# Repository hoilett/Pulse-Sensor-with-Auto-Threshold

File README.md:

# Pulse-Sensor-with-Auto-Threshold

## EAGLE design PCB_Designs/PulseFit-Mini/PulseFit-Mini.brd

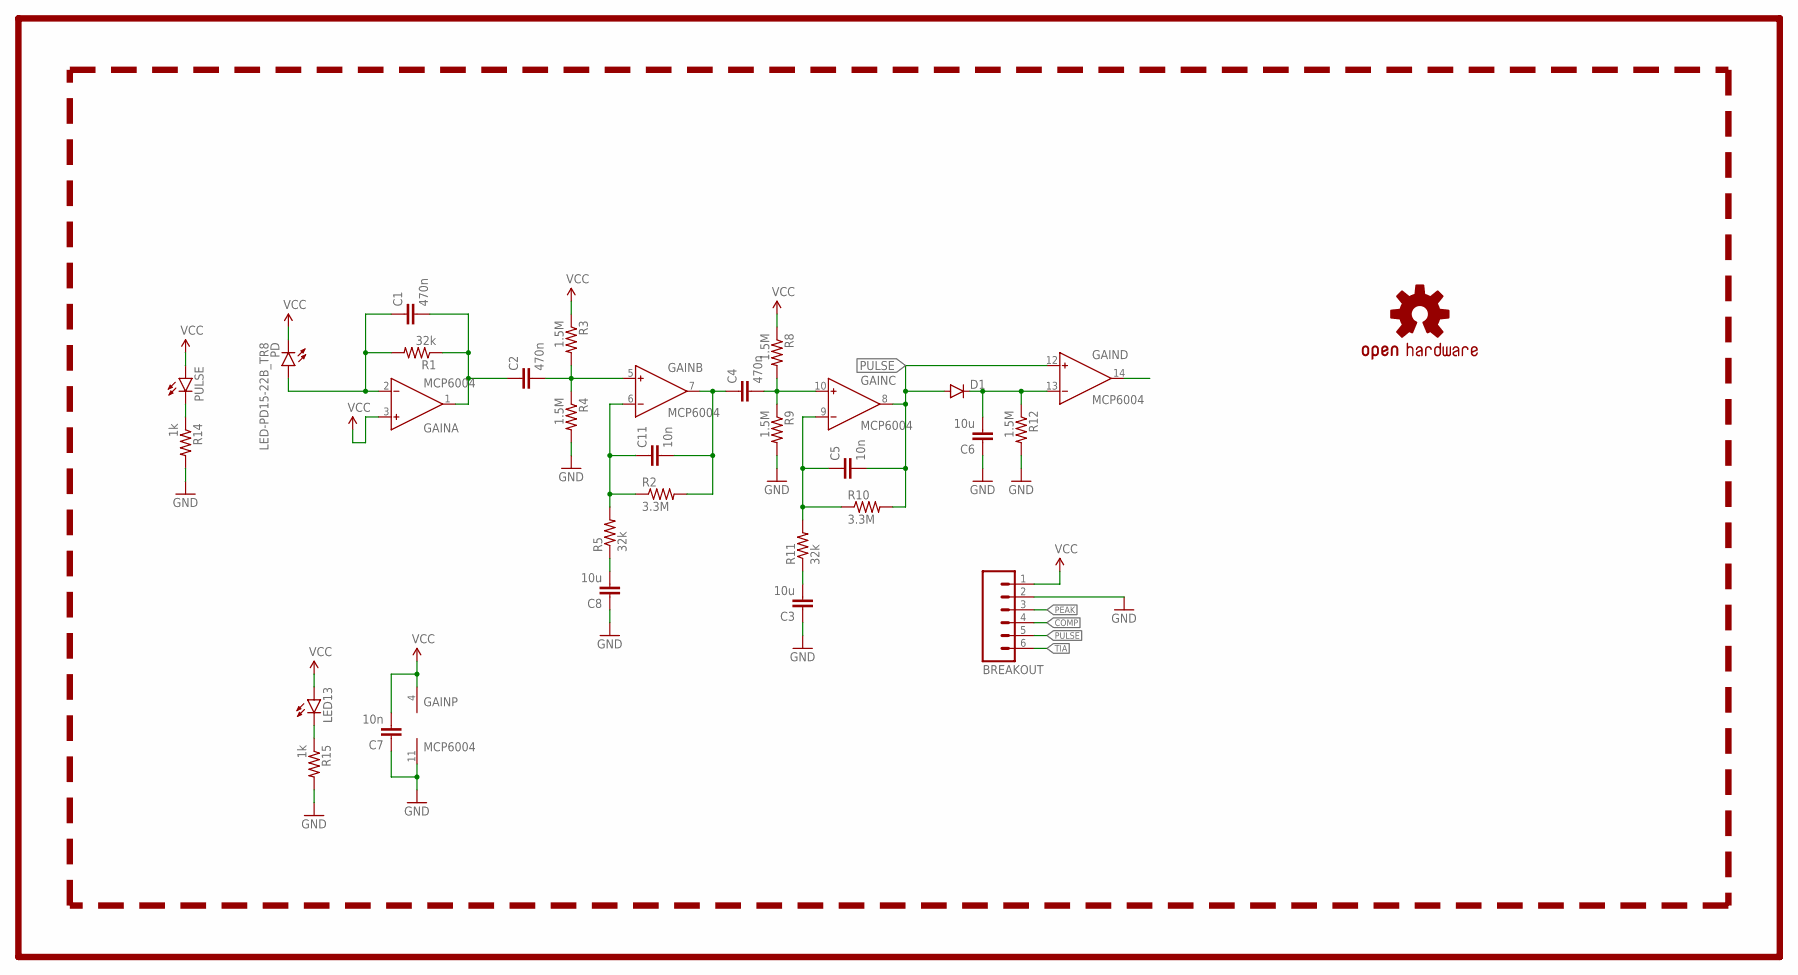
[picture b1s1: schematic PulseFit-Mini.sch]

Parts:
BREAKOUT: M06NO_SILK_FEMALE_PTH; 1X06_NO_SILK
C1, C2, C4: 470n; C0402
C3, C6, C8: 10u; C0805
C5, C7, C11: 10n; C0402
D1: 250mA/100V; SOD-323
GAIN: MCP6004; TSSOP14
LED13: LED0603; LED-0603
LOGO1: OSHW-LOGOS; OSHW-LOGO-S
PD: LED-PD15-22B_TR8
PULSE: LED0603; LED-0603
R1, R5, R11: 32k; R0402
R2, R10: 3.3M; R0402
R3, R4, R8, R9, R12: 1.5M; R0402
R14, R15: 1k; R0402

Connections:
COMP: BREAKOUT.4, GAIN.14 (OUT)
GND: BREAKOUT.2, C3.1, C6.1, C7.1, C8.1, GAIN.11 (V-), R4.2, R9.2, R12.2, R14.2, R15.2
unnamed: C1.1, GAIN.2 (IN-), PD.A-1 (A), PD.A-2 (A), R1.2
unnamed: C4.2, GAIN.10 (IN+), R8.2, R9.1
unnamed: C2.2, GAIN.5 (IN+), R3.2, R4.1
unnamed: C3.2, R11.1
unnamed: C5.1, GAIN.9 (IN-), R10.1, R11.2
unnamed: PULSE.C, R14.1
unnamed: C11.1, GAIN.6 (IN-), R2.1, R5.2
unnamed: C4.1, C11.2, GAIN.7 (OUT), R2.2
unnamed: LED13.C, R15.1
unnamed: C8.2, R5.1
PEAK: BREAKOUT.3, C6.2, D1.C, GAIN.13 (IN-), R12.1
PULSE: BREAKOUT.5, C5.2, D1.A, GAIN.8 (OUT), GAIN.12 (IN+), R10.2
TIA: BREAKOUT.6, C1.2, C2.1, GAIN.1 (OUT), R1.1
VCC: BREAKOUT.1, C7.2, GAIN.3 (IN+), GAIN.4 (V+), LED13.A, PD.C-1 (C), PD.C-2 (C), PULSE.A, R3.1, R8.1

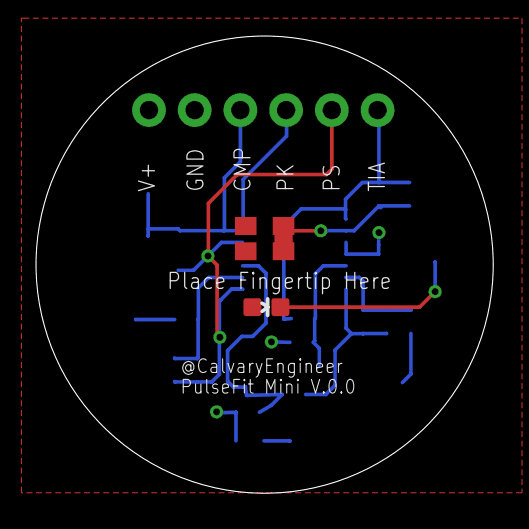
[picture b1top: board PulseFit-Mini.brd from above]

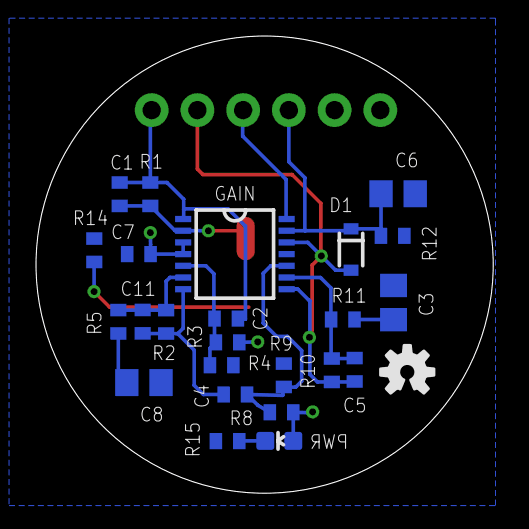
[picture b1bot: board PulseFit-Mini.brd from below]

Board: 2 copper layers, 25.4 x 25.4 mm, 28 parts (25 on the bottom side), 16 nets.

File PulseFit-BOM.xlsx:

PulseFit V.4.0
BOM # | Comment | Description | Mounting Type | Package | Designator | Manufacturer | Manufacturer Part Number | Quantity | Supplier | Supplier Part Number | Price per unit | Price Total
1 | IR LED | 940nm, 0.2mW/sr @ 20mA | SMD | 0603 | PULSE | Everlight Electronics Co Ltd | IR19-21C/TR8 | 1 | Digi-Key | 1080-1354-1-ND | 0.5 | 0.5
2 | IR Photodiode | Photodiode, 940nm, 730nm-1100nm | SMD | 4-SMD, No Lead | PD | Everlight Electronics Co Ltd | PD15-22B/TR8 | 1 | Digi-Key | 1080-1366-1-ND | 0.56999999999999995 | 0.56999999999999995
3 | MCP6004 | Rail-to-Rail Input and Output, Single Supply, Quad Op Amp | SMD | 14-TSSOP | Gain | Microchip Technology | MCP6004T-I/ST | 1 | Digi-Key | MCP6004T-I/STCT-ND | 0.44 | 0.44
4 | Coin Cell Battery Holder | Coin, 20.0mm | SMD | SMD (SMT) Tab | BATT-CR2032 | MPD (Memory Protection Devices) | BK-883-TR | 1 | Digi-Key | BK-883-CT-ND | 0.52 | 0.52
5 | Heart beat indicaator | Red LED, 2V, 621nm, 130degree | SMD-Bottom Entry | 1206 | LD1, LD2, LD3, LD4, LD5, LD6, LD7, LD8, LD9, LD10, LD11, LD12, LD13, LD14, LD15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 | Lite-On Inc. | LTST-C230KRKT | 19 | Digi-Key | 160-1457-1-ND | 0.34 | 6.4600000000000009
6 | Power Switch | Slide Switch, On-On, 300mA (DC), 6V | SMD | J Lead | POWER | C&K Components | JS202011JCQN | 1 | Digi-Key | CKN10723CT-ND | 0.48 | 0.48
7 | Diode | General purpose, small-signal | SMD | SOD-323F | D1 | Panasonic Electronic Components | DA2J10400L | 1 | Digi-Key | DA2J10400LCT-ND | 0.1 | 0.1
8 | 32k | 1%, 1/16 W | SMD | 0402 | R1,R5,R11 | Samsung Electro-Mechanics America, Inc. | RC1005F333CS | 3 | Digi-Key | 1276-3461-1-ND | 0.1 | 0.30000000000000004
9 | 10nF | 10%, 50V, X7R | SMD | 0402 | C5,C11,C7 | Samsung Electro-Mechanics America, Inc. | CL05B103KB5NNNC | 3 | Digi-Key | 1276-1028-1-ND | 0.1 | 0.30000000000000004
10 | 3.3M | 1%, 1/16 W | SMD | 0402 | R2,R10 | Yageo | RC0402FR-073M3L | 2 | Digi-Key | 311-3.30MLRCT-ND | 0.08 | 0.16
11 | 1.47M | 1%, 1/16 W | SMD | 0402 | R3,R4,R8,R9,R12 | Samsung Electro-Mechanics America, Inc. | RC1005F1474CS | 5 | Digi-Key | 1276-4291-1-ND | 0.1 | 0.5
12 | 10uF | 10%, 10V, X5R | SMD | 0805 | C3,C6,C8 | Samsung Electro-Mechanics America, Inc. | CL21A106KPFNNNG | 3 | Digi-Key | 1276-6456-1-ND | 0.11 | 0.33
13 | 1k | 1%, 1/16 W | SMD | 0402 | R14,R15 | Yageo | RC0402FR-071KL | 2 | Digi-Key | 311-1.00KLRCT-ND | 0.1 | 0.2
14 | 169 Ohms | 1%, 1/16 W | SMD | 0402 | R13 | Yageo | RC0402FR-07169RL | 1 | Digi-Key | YAG3001CT-ND | 0.1 | 0.1
15 | 0.47 uF | 10%, 35V, X5R | SMD | 0402 | C1,C2,C4 | Murata Electronics North America | GRM155R6YA474KE01D | 3 | Digi-Key | 490-10462-1-ND | 0.1 | 0.30000000000000004
 |  |  |  |  |  |  |  |  |  |  |  | 11.260000000000002

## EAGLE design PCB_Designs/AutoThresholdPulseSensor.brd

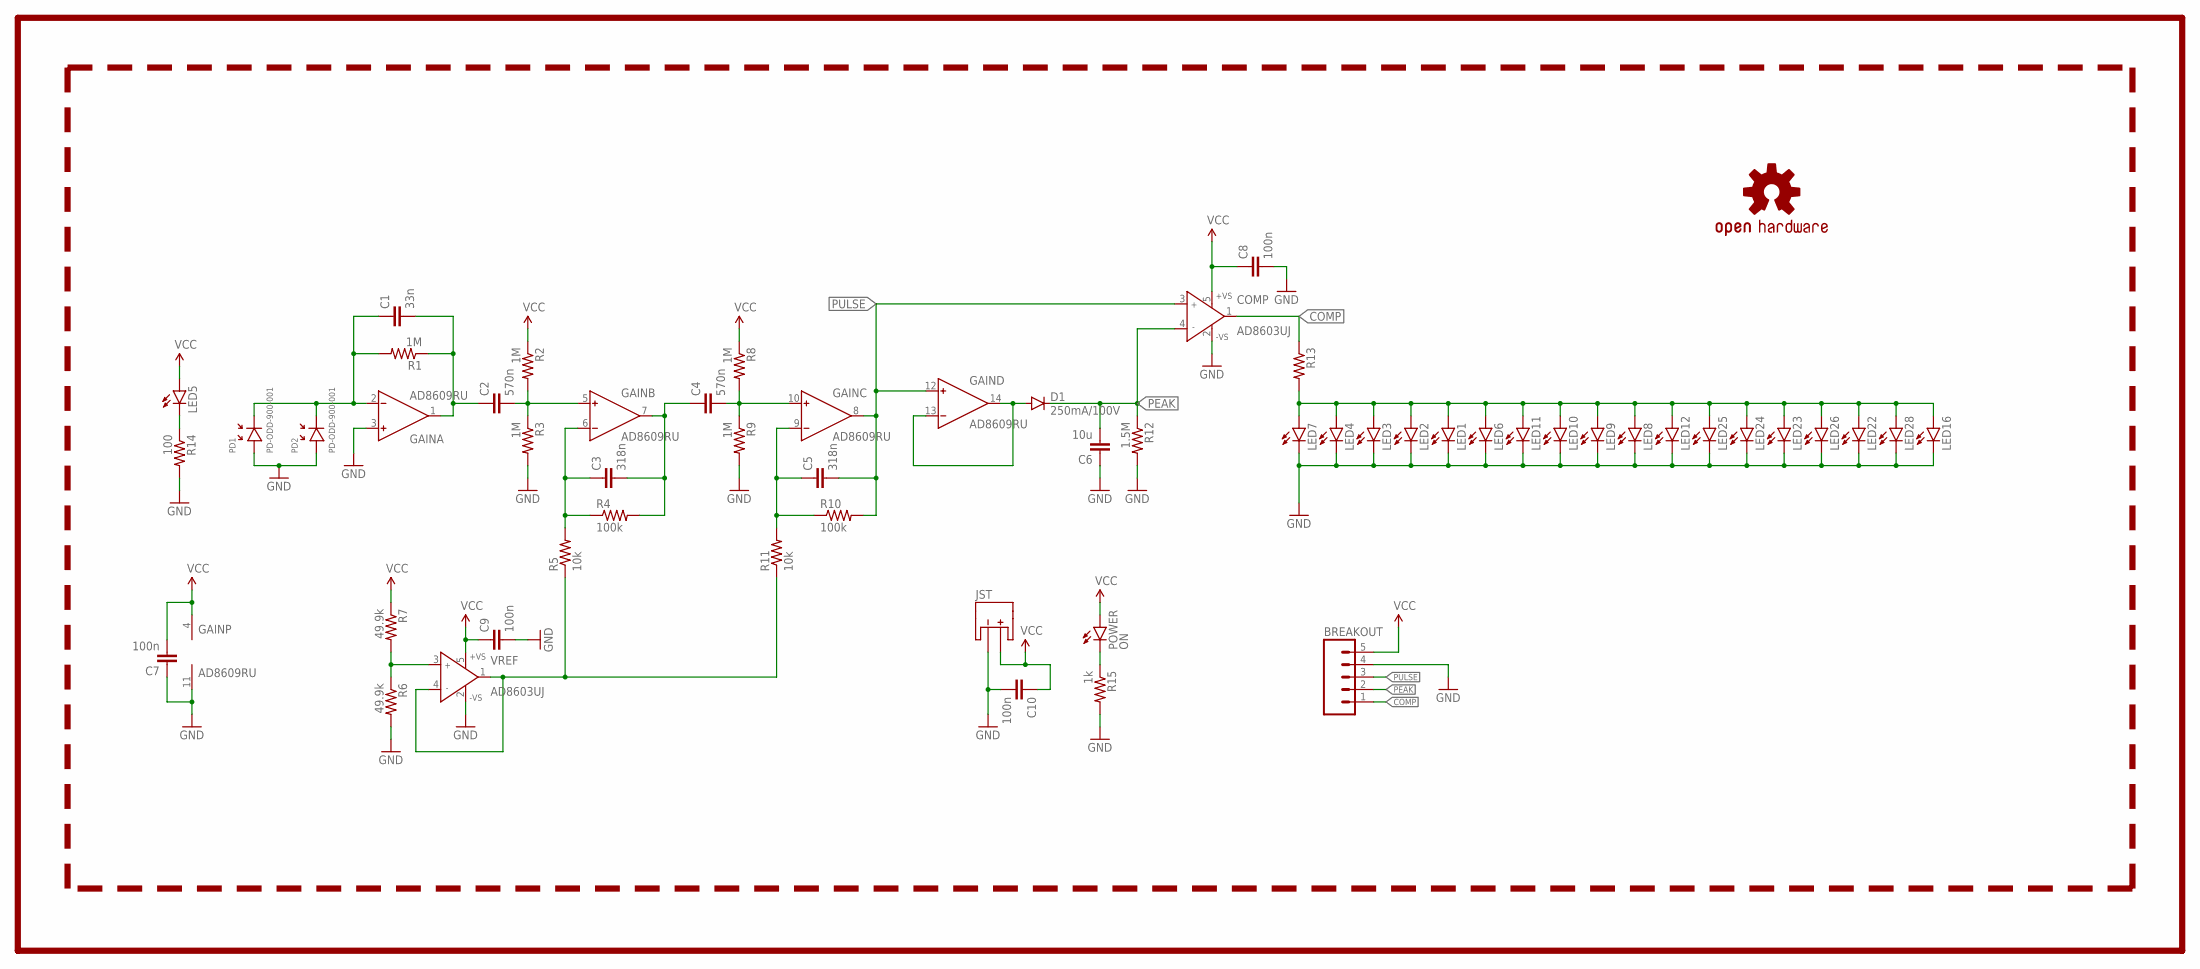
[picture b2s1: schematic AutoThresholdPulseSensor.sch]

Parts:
BREAKOUT: M05NO_SILK; 1X05_NO_SILK
C1: 33n; C0402
C2, C4: 570n; C0402
C3, C5: 318n; C0402
C6: 10u; C0402
C7, C8, C9, C10: 100n; C0402
COMP: AD8603UJ; SOT23-5
D1: 250mA/100V; SOD-323
GAIN: AD8609RU; TSSOP14
JST: JST-PTH; JST-2-PTH-VERT
LED1, LED2, LED3, LED4, LED6, LED7, LED8, LED9, LED10, LED11, LED12, LED16, LED22, LED23, LED24, LED25, LED26, LED28: LED5MM
LED5: LED0603; LED-0603
LOGO1: OSHW-LOGOS; OSHW-LOGO-S
PD1, PD2: PD-ODD-900-001; SMD-PD-01
POWER: ON; LED-0603
R1, R2, R3, R8, R9: 1M; R0402
R4, R10: 100k; R0402
R5, R11: 10k; R0402
R6, R7: 49.9k; R0402
R12: 1.5M; R0402
R13: R-US_R0402; R0402
R14: 100; R0402
R15: 1k; R0402
VREF: AD8603UJ; SOT23-5

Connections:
1/2-VDD: R5.1, R11.1, VREF.1 (OUT), VREF.4 (IN-)
ANODE: LED1.A, LED2.A, LED3.A, LED4.A, LED6.A, LED7.A, LED8.A, LED9.A, LED10.A, LED11.A, LED12.A, LED16.A, LED22.A, LED23.A, LED24.A, LED25.A, LED26.A, LED28.A, R13.2
COMP: BREAKOUT.1, COMP.1 (OUT), R13.1
GND: BREAKOUT.4, C6.1, C7.1, C8.2, C9.2, C10.2, COMP.2 (-VS), GAIN.3 (IN+), GAIN.11 (V-), JST.-, LED1.K (C), LED2.K (C), LED3.K (C), LED4.K (C), LED6.K (C), LED7.K (C), LED8.K (C), LED9.K (C), LED10.K (C), LED11.K (C), LED12.K (C), LED16.K (C), LED22.K (C), LED23.K (C), LED24.K (C), LED25.K (C), LED26.K (C), LED28.K (C), PD1.ANODE (+), PD2.ANODE (+), R3.2, R6.2, R9.2, R12.2, R14.2, R15.2, VREF.2 (-VS)
unnamed: C1.1, GAIN.2 (IN-), PD1.CATHODE (-), PD2.CATHODE (-), R1.2
unnamed: C1.2, C2.1, GAIN.1 (OUT), R1.1
unnamed: C4.2, GAIN.10 (IN+), R8.2, R9.1
unnamed: C2.2, GAIN.5 (IN+), R2.2, R3.1
unnamed: C3.1, GAIN.6 (IN-), R4.1, R5.2
unnamed: C3.2, C4.1, GAIN.7 (OUT), R4.2
unnamed: R6.1, R7.2, VREF.3 (IN+)
unnamed: C5.1, GAIN.9 (IN-), R10.1, R11.2
unnamed: LED5.C, R14.1
unnamed: D1.A, GAIN.13 (IN-), GAIN.14 (OUT)
unnamed: POWER.C, R15.1
PEAK: BREAKOUT.2, C6.2, COMP.4 (IN-), D1.C, R12.1
PULSE: BREAKOUT.3, C5.2, COMP.3 (IN+), GAIN.8 (OUT), GAIN.12 (IN+), R10.2
VCC: BREAKOUT.5, C7.2, C8.1, C9.1, C10.1, COMP.5 (+VS), GAIN.4 (V+), JST.+, LED5.A, POWER.A, R2.1, R7.1, R8.1, VREF.5 (+VS)

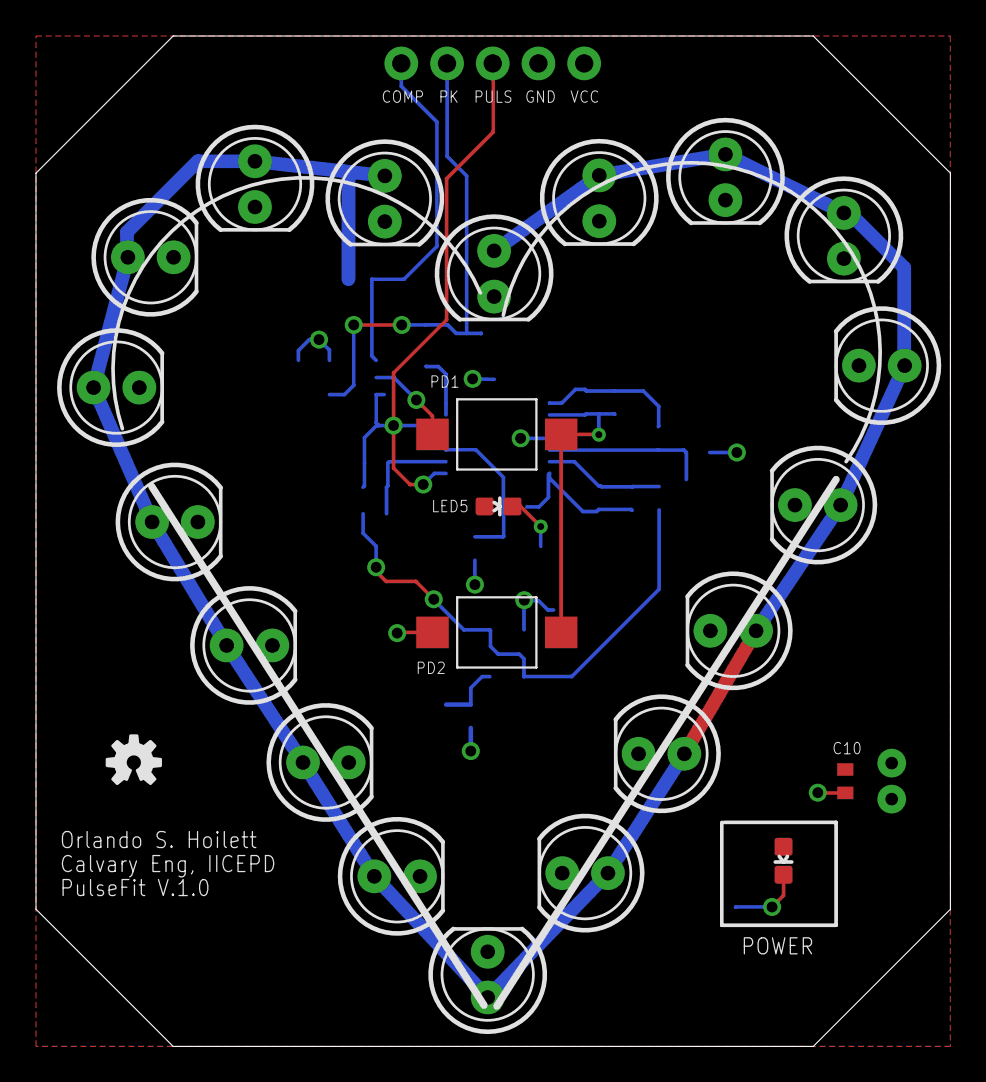
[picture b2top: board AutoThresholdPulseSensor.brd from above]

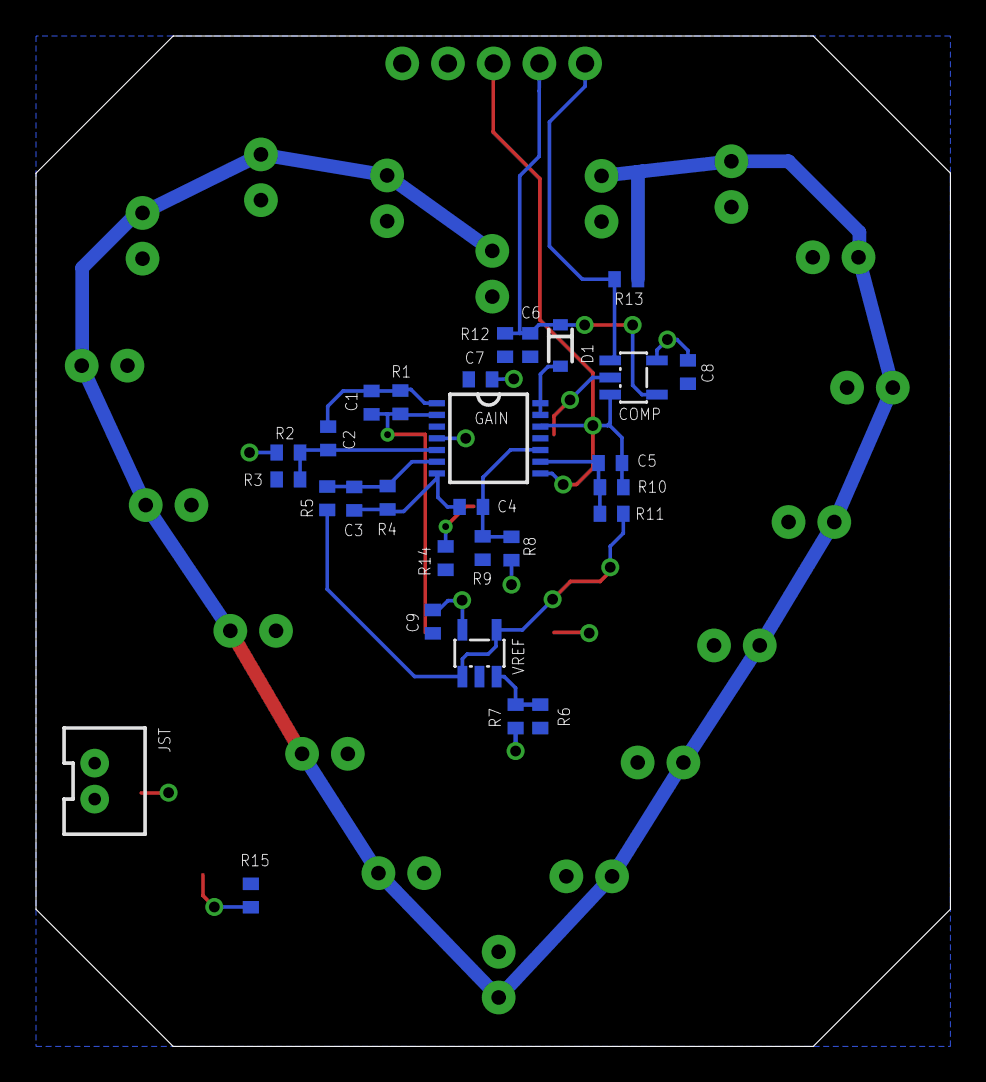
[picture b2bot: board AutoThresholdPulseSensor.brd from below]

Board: 2 copper layers, 50.8 x 56.1 mm, 54 parts (29 on the bottom side), 18 nets.

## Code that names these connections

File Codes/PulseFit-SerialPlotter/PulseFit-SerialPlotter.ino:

/*  FILENAME: PulseFit-Plotter
 *  AUTHORS:  Orlando S. Hoilett
 *  VERSION:  V.0.1.0
 *  EMAIL:    orlandohoilett@gmail.com
 *  WEBSITE:  https://github.com/hoilett/Pulse-Sensor-with-Auto-Threshold.git
 *  
 *  AFFILIATION
 *  Calvary Engineering (@CalvEngIO)
 *  
 *  Description
 *  
 *  
 *  LICENSE
 *  CC-BY-SA-4.0
 *  
 *  If you find any bugs or have any questions, please feel free to contact
 *  orlandohoilett@gmail.com
 *  
 */


int pulsePin = A0;
int compPin = A1;
int peakPin = A2;

int pulse = 0;
int comp = 0;
int peak = 0;

void setup()
{
  Serial.begin(9600);

  //uncomment this line if you want to reference the analogRead
  //to V+ of PulseFit if not being powered from Arduino
  //analogReference(EXTERNAL);

}

void loop()
{
  //measuring the amplifier outputs using the ADC
  pulse = analogRead(pulsePin);
  comp = analogRead(compPin);
  peak = analogRead(peakPin);

  //The Arduino Serial Plotter can only plot one variable
  //at a time. Uncomment and comment each line for whatever value
  //you would like to print.
  Serial.println(pulse);
  //Serial.print(comp);
  //Serial.print(peak);

  delay(20);
}

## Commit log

2016-07-05 almost done
2016-07-09 finished first version of board design
2016-07-15 added zip for OSH Park order
2016-09-10 Create LICENSE
2016-09-10 added previous OSHPark Orders
2016-09-11 updated PulseFit BOM and added disclaimer in schematic
2016-09-11 made correction to BOM to reflect coin cell holder and deleted old BOM
2016-09-11 new derivatives of PulseFit and folder organization
2016-09-12 updated BOM for PulseFit Mini
2016-09-19 working on some Arduino codes for PulseFit. Untested at the moment
2016-09-19 Rename LICENSE to LICENSE-hardware
2016-09-19 Create LICENSE-software
2016-11-05 prototype code

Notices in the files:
PCB_Designs/AutoThresholdPulseSensor.sch:
Creative Commons License
parts and their libraries:
SparkFun-DiscreteSemi: Licensing: Creative Commons ShareAlike 4.0 International - https://creativecommons.org/licenses/by-sa/4.0
